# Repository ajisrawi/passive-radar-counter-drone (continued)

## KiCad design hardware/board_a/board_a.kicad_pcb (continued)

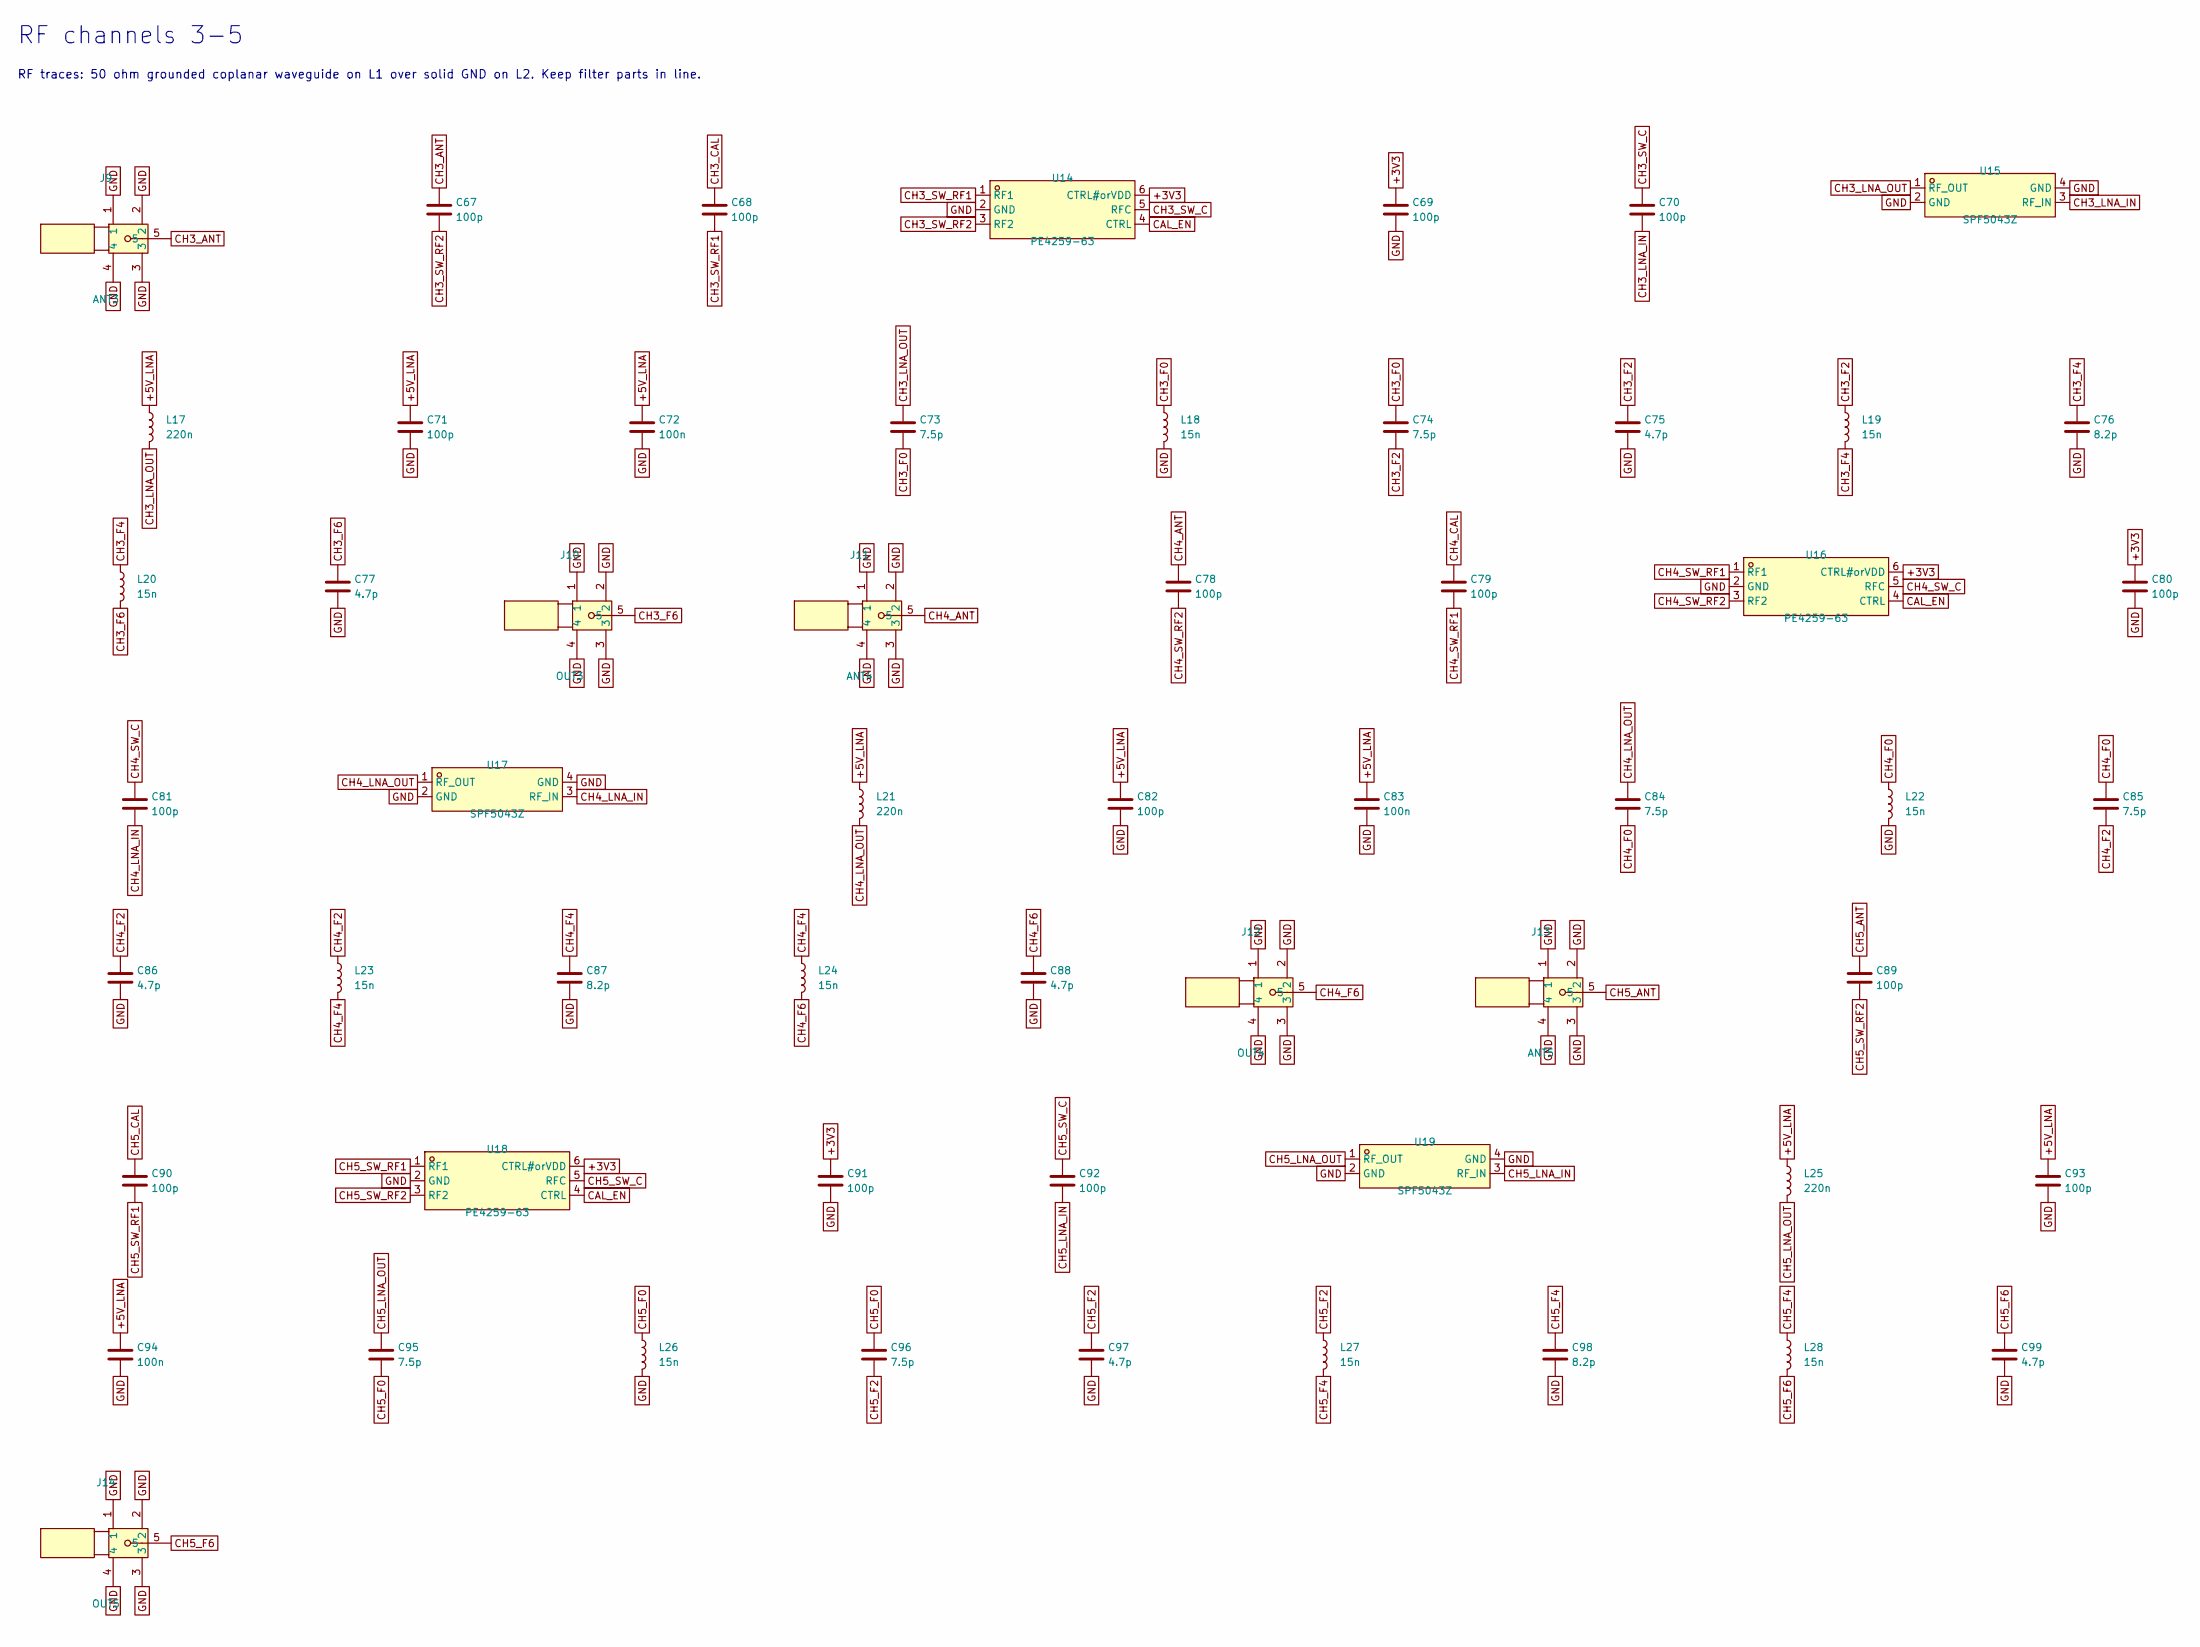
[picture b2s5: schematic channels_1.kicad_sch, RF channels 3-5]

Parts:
C67, C68, C69, C70, C71, C78, C79, C80, C81, C82, C89, C90, C91, C92, C93: 100p; C_0402_1005Metric
C72, C83, C94: 100n; C_0402_1005Metric; LCSC C1525
C73, C74, C84, C85, C95, C96: 7.5p; C_0402_1005Metric
C75, C77, C86, C88, C97, C99: 4.7p; C_0402_1005Metric
C76, C87, C98: 8.2p; C_0402_1005Metric
J9: ANT3; SMA-TH_BWSMA-KE-Z001; MPN BWSMA-KE-Z001; LCSC C496549
J10: OUT3; SMA-TH_BWSMA-KE-Z001; MPN BWSMA-KE-Z001; LCSC C496549
J11: ANT4; SMA-TH_BWSMA-KE-Z001; MPN BWSMA-KE-Z001; LCSC C496549
J12: OUT4; SMA-TH_BWSMA-KE-Z001; MPN BWSMA-KE-Z001; LCSC C496549
J13: ANT5; SMA-TH_BWSMA-KE-Z001; MPN BWSMA-KE-Z001; LCSC C496549
J14: OUT5; SMA-TH_BWSMA-KE-Z001; MPN BWSMA-KE-Z001; LCSC C496549
L17, L21, L25: 220n; L_0603_1608Metric
L18, L19, L20, L22, L23, L24, L26, L27, L28: 15n; L_0402_1005Metric
U14, U16, U18: PE4259-63; SC-70-6_L2.2-W1.3-P0.65-LS2.1-BL; MPN PE4259-63; LCSC C470892
U15, U17, U19: SPF5043Z; SOT343_L2.0-W1.3-P1.30-LS2.1-BL; MPN SPF5043Z; LCSC C470902

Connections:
+3V3: C69.1, C80.1, C91.1, U14.6 (CTRL#orVDD), U16.6 (CTRL#orVDD), U18.6 (CTRL#orVDD); also elsewhere on the board
+5V_LNA: C71.1, C72.1, C82.1, C83.1, C93.1, C94.1, L17.1, L21.1, L25.1; also elsewhere on the board
CAL_EN: U14.4 (CTRL), U16.4 (CTRL), U18.4 (CTRL); also elsewhere on the board
CH3_ANT: C67.1, J9.5
CH3_CAL: C68.1; also elsewhere on the board
CH3_F0: C73.2, C74.1, L18.1
CH3_F2: C74.2, C75.1, L19.1
CH3_F4: C76.1, L19.2, L20.1
CH3_F6: C77.1, J10.5, L20.2
CH3_LNA_IN: C70.2, U15.3 (RF_IN)
CH3_LNA_OUT: C73.1, L17.2, U15.1 (RF_OUT)
CH3_SW_C: C70.1, U14.5 (RFC)
CH3_SW_RF1: C68.2, U14.1 (RF1)
CH3_SW_RF2: C67.2, U14.3 (RF2)
CH4_ANT: C78.1, J11.5
CH4_CAL: C79.1; also elsewhere on the board
CH4_F0: C84.2, C85.1, L22.1
CH4_F2: C85.2, C86.1, L23.1
CH4_F4: C87.1, L23.2, L24.1
CH4_F6: C88.1, J12.5, L24.2
CH4_LNA_IN: C81.2, U17.3 (RF_IN)
CH4_LNA_OUT: C84.1, L21.2, U17.1 (RF_OUT)
CH4_SW_C: C81.1, U16.5 (RFC)
CH4_SW_RF1: C79.2, U16.1 (RF1)
CH4_SW_RF2: C78.2, U16.3 (RF2)
CH5_ANT: C89.1, J13.5
CH5_CAL: C90.1; also elsewhere on the board
CH5_F0: C95.2, C96.1, L26.1
CH5_F2: C96.2, C97.1, L27.1
CH5_F4: C98.1, L27.2, L28.1
CH5_F6: C99.1, J14.5, L28.2
CH5_LNA_IN: C92.2, U19.3 (RF_IN)
CH5_LNA_OUT: C95.1, L25.2, U19.1 (RF_OUT)
CH5_SW_C: C92.1, U18.5 (RFC)
CH5_SW_RF1: C90.2, U18.1 (RF1)
CH5_SW_RF2: C89.2, U18.3 (RF2)
GND: C69.2, C71.2, C72.2, C75.2, C76.2, C77.2, C80.2, C82.2, C83.2, C86.2, C87.2, C88.2, C91.2, C93.2, C94.2, C97.2, C98.2, C99.2, J9.1, J9.2, J9.3, J9.4, J10.1, J10.2, J10.3, J10.4, J11.1, J11.2, J11.3, J11.4, J12.1, J12.2, J12.3, J12.4, J13.1, J13.2, J13.3, J13.4, J14.1, J14.2, J14.3, J14.4, L18.2, L22.2, L26.2, U14.2 (GND), U15.2 (GND), U15.4 (GND), U16.2 (GND), U17.2 (GND), U17.4 (GND), U18.2 (GND), U19.2 (GND), U19.4 (GND); also elsewhere on the board

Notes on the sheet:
RF channels 3-5
RF traces: 50 ohm grounded coplanar waveguide on L1 over solid GND on L2. Keep filter parts in line.

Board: 4 copper layers, 194 parts (0 on the bottom side), 98 nets, no tracks yet.

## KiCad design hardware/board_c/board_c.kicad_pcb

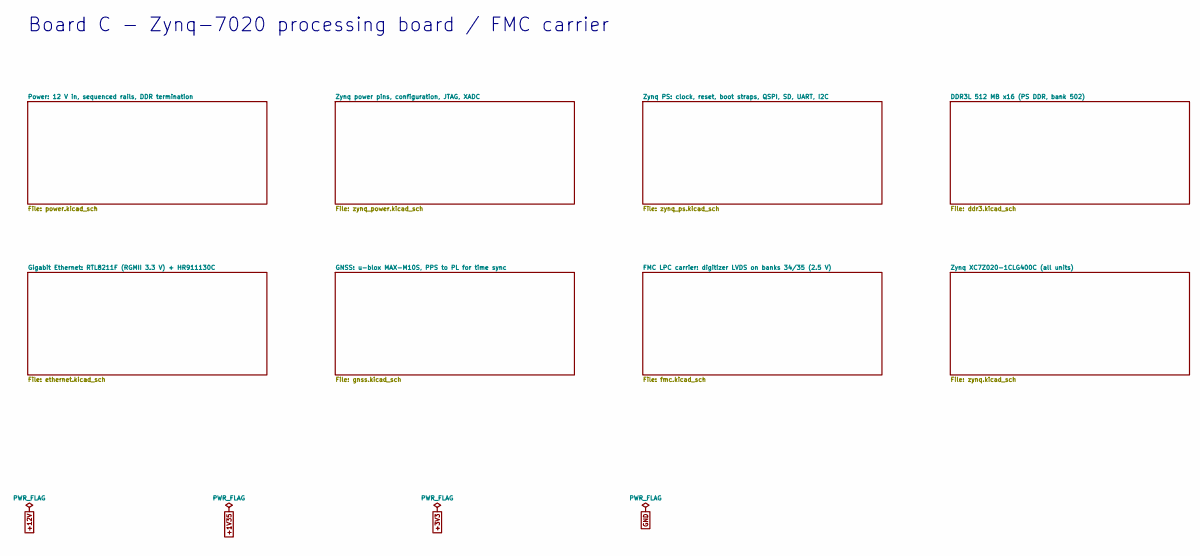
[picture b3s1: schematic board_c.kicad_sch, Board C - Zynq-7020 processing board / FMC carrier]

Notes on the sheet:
Board C - Zynq-7020 processing board / FMC carrier

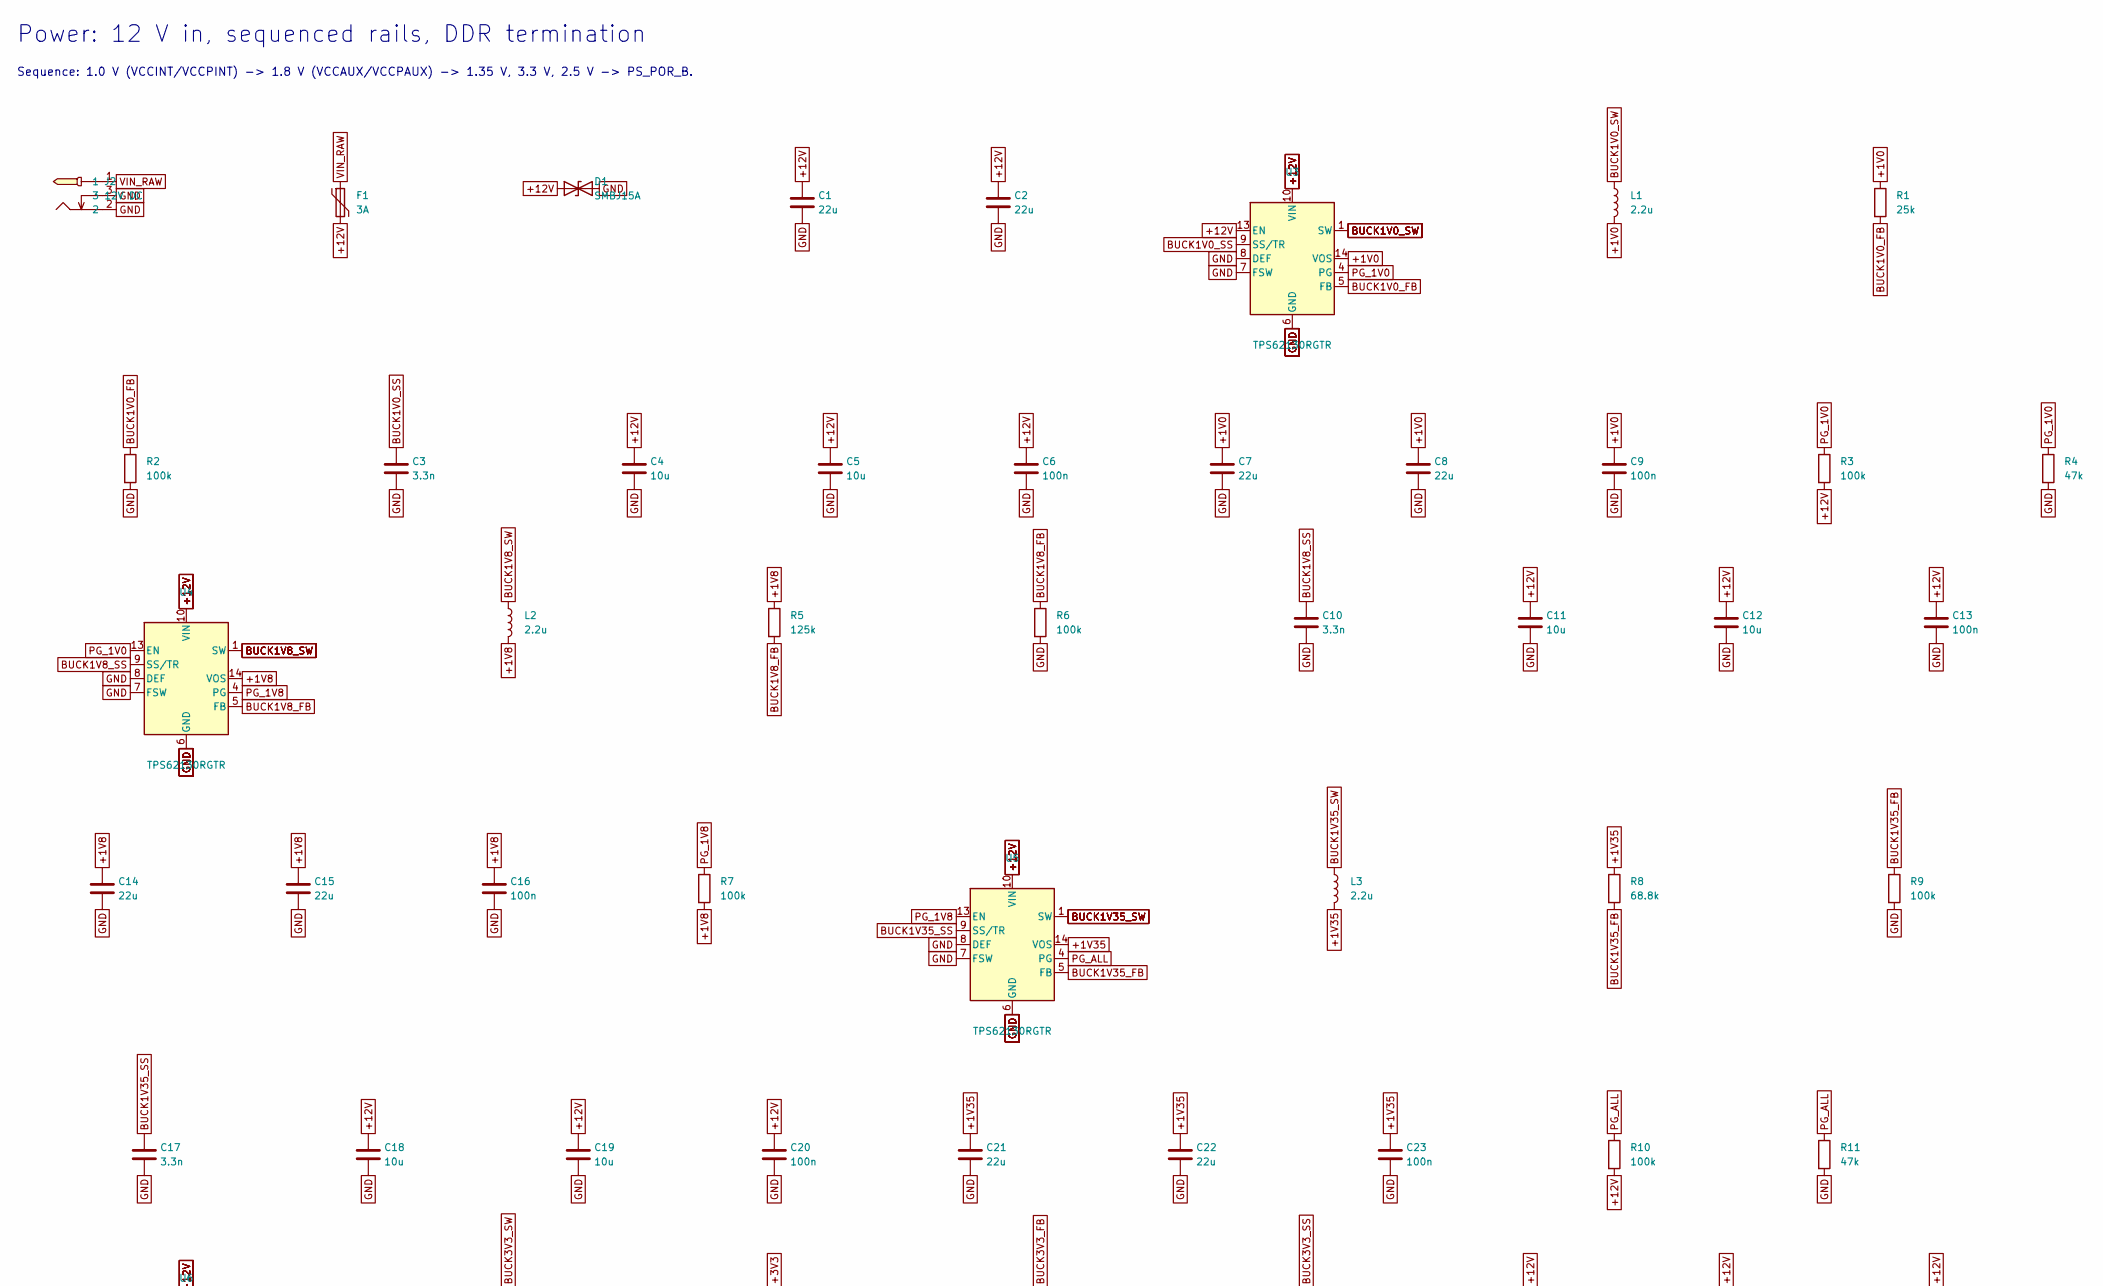
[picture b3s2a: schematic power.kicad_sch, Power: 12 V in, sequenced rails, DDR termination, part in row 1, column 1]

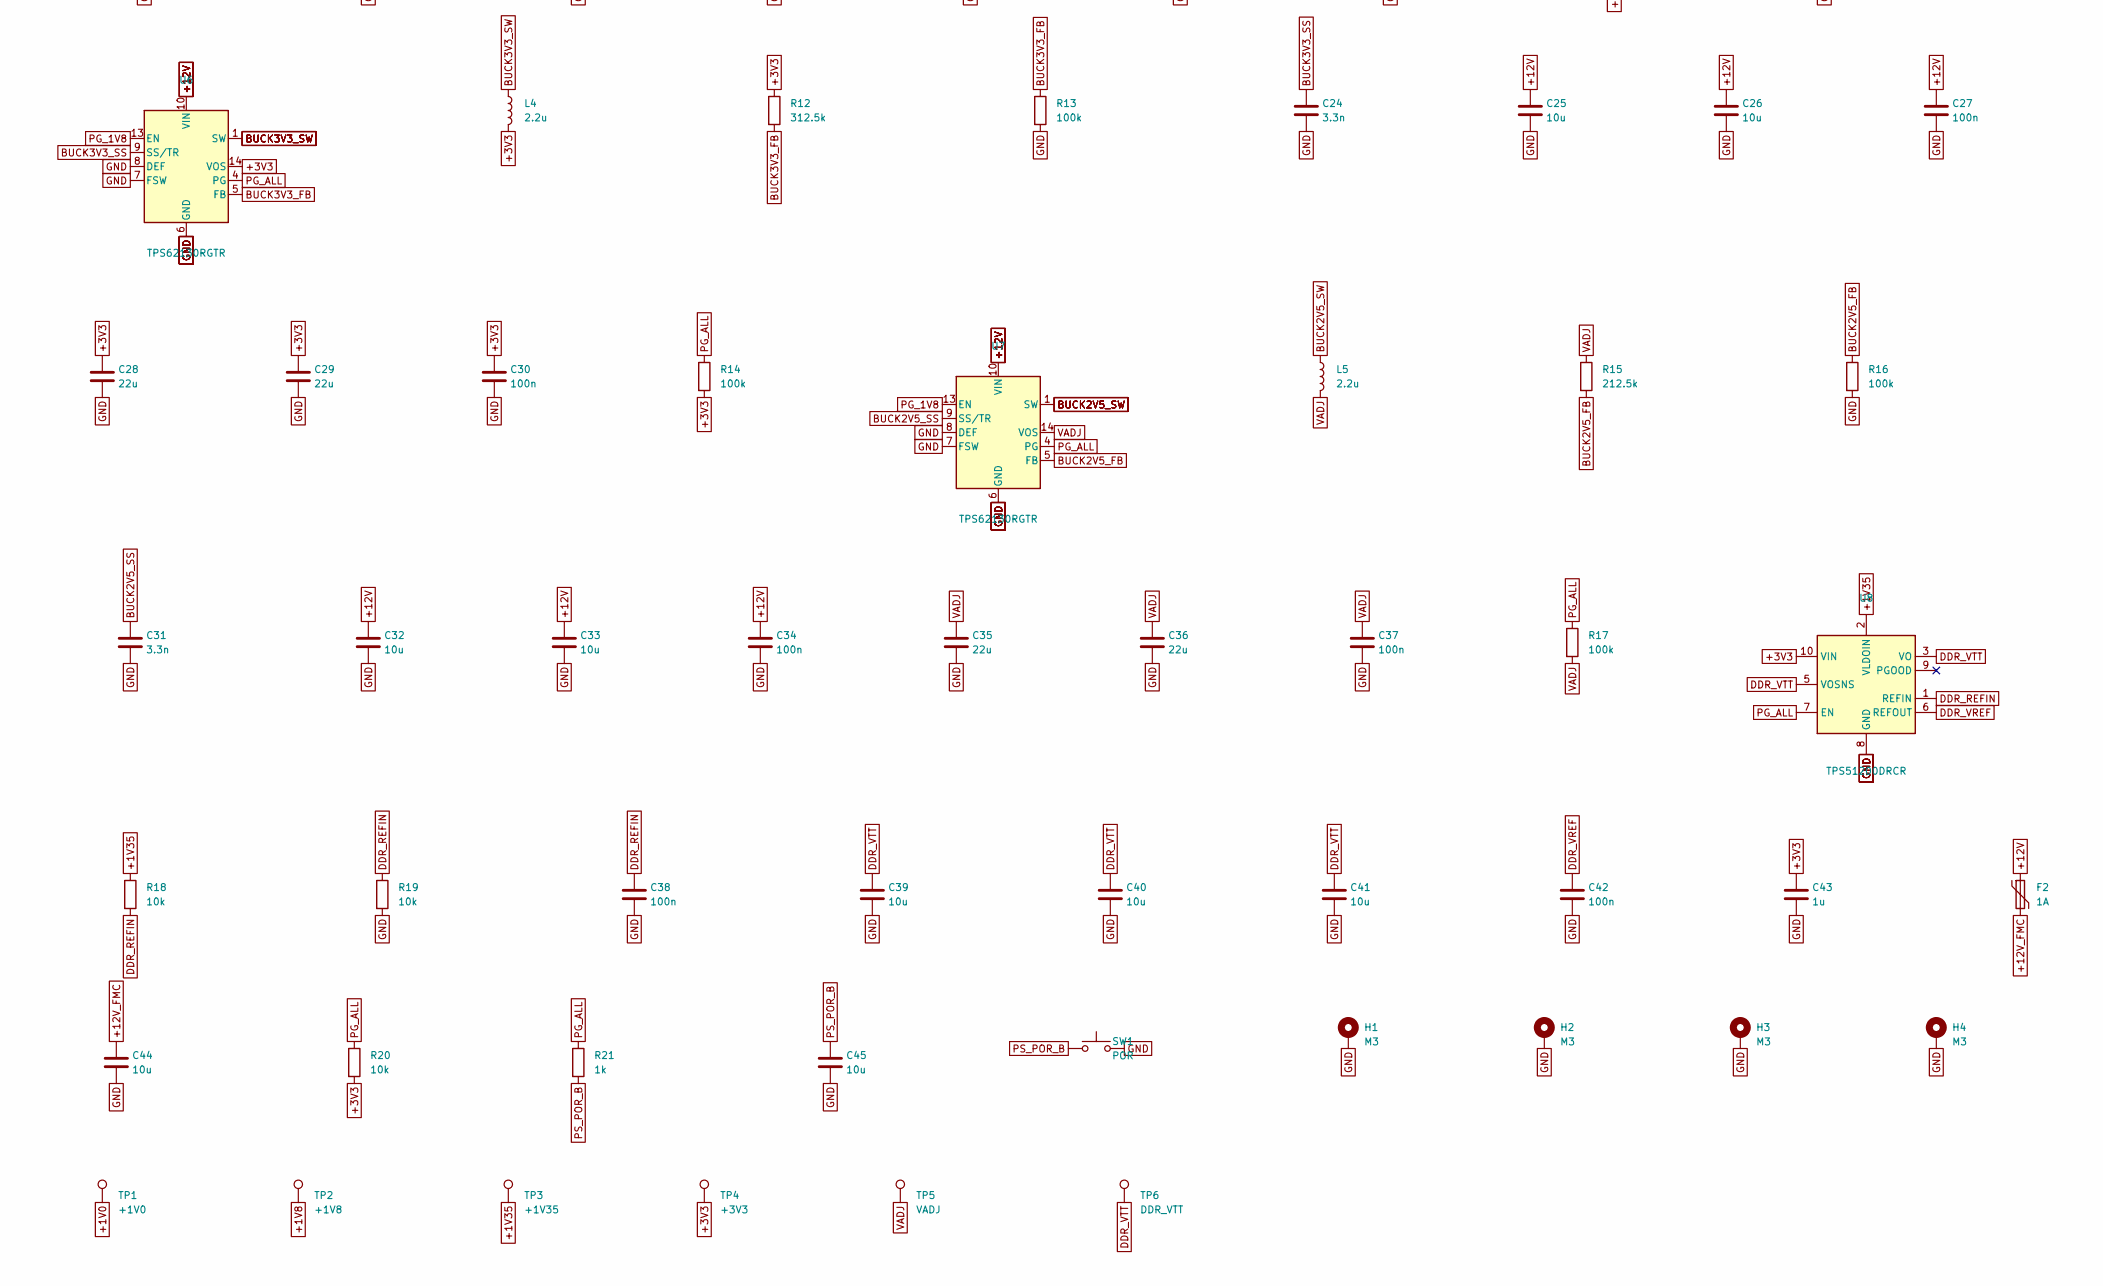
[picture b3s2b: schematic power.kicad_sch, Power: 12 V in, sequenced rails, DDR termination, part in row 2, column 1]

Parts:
C1, C2: 22u; C_1206_3216Metric
C3, C10, C17, C24, C31: 3.3n; C_0402_1005Metric
C4, C5, C11, C12, C18, C19, C25, C26, C32, C33, C44: 10u; C_0805_2012Metric
C6, C9, C13, C16, C20, C23, C27, C30, C34, C37, C38, C42: 100n; C_0402_1005Metric; LCSC C1525
C7, C8, C14, C15, C21, C22, C28, C29, C35, C36: 22u; C_0805_2012Metric; LCSC C45783
C39, C40, C41, C45: 10u; C_0603_1608Metric; LCSC C19702
C43: 1u; C_0402_1005Metric; LCSC C52923
D1: SMBJ15A; D_SMB
F1: 3A; Fuse_1206_3216Metric
F2: 1A; Fuse_1206_3216Metric
H1, H2, H3, H4: M3; MountingHole_3.2mm_M3_Pad_Via
J2: 12V DC; DC-IN-TH_DC-005C-20A; MPN DC-005C-20A; LCSC C84007
L1, L2, L3, L4, L5: 2.2u; L_Bourns-SRN4018; MPN SRN4018-2R2M
R1: 25k; R_0402_1005Metric
R2, R3, R6, R7, R9, R10, R13, R14, R16, R17: 100k; R_0402_1005Metric; LCSC C25741
R4, R11: 47k; R_0402_1005Metric
R5: 125k; R_0402_1005Metric
R8: 68.8k; R_0402_1005Metric
R12: 312.5k; R_0402_1005Metric
R15: 212.5k; R_0402_1005Metric
R18, R19: 10k; R_0402_1005Metric; Tolerance 1%; LCSC C25744
R20: 10k; R_0402_1005Metric; LCSC C25744
R21: 1k; R_0402_1005Metric; LCSC C11702
SW1: POR; SW_SPST_TL3342
TP1: +1V0; TestPoint_Pad_D1.0mm
TP2: +1V8; TestPoint_Pad_D1.0mm
TP3: +1V35; TestPoint_Pad_D1.0mm
TP4: +3V3; TestPoint_Pad_D1.0mm
TP5: VADJ; TestPoint_Pad_D1.0mm
TP6: DDR_VTT; TestPoint_Pad_D1.0mm
U3, U4, U5, U6, U7: TPS62130RGTR; VQFN-16-1EP_3x3mm_P0.5mm_EP1.68x1.68mm; MPN TPS62130RGTR; LCSC C43590
U8: TPS51200DRCR; VSON-10-1EP_3x3mm_P0.5mm_EP1.65x2.4mm; LCSC C34771

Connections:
+1V0: C7.1, C8.1, C9.1, L1.2, R1.1, TP1.1, U3.14 (VOS); also elsewhere on the board
+1V8: C14.1, C15.1, C16.1, L2.2, R5.1, R7.2, TP2.1, U4.14 (VOS); also elsewhere on the board
+1V35: C21.1, C22.1, C23.1, L3.2, R8.1, R18.1, TP3.1, U5.14 (VOS), U8.2 (VLDOIN); also elsewhere on the board
+3V3: C28.1, C29.1, C30.1, C43.1, L4.2, R12.1, R14.2, R20.2, TP4.1, U6.14 (VOS), U8.10 (VIN); also elsewhere on the board
+12V: C1.1, C2.1, C4.1, C5.1, C6.1, C11.1, C12.1, C13.1, C18.1, C19.1, C20.1, C25.1, C26.1, C27.1, C32.1, C33.1, C34.1, D1.1 (A1), F1.2, F2.1, R3.2, R10.2, U3.10 (VIN), U3.11 (VIN), U3.12 (VIN), U3.13 (EN), U4.10 (VIN), U4.11 (VIN), U4.12 (VIN), U5.10 (VIN), U5.11 (VIN), U5.12 (VIN), U6.10 (VIN), U6.11 (VIN), U6.12 (VIN), U7.10 (VIN), U7.11 (VIN), U7.12 (VIN)
+12V_FMC: C44.1, F2.2; also elsewhere on the board
BUCK1V0_FB: R1.2, R2.1, U3.5 (FB)
BUCK1V0_SS: C3.1, U3.9 (SS/TR)
BUCK1V0_SW: L1.1, U3.1 (SW), U3.2 (SW), U3.3 (SW)
BUCK1V8_FB: R5.2, R6.1, U4.5 (FB)
BUCK1V8_SS: C10.1, U4.9 (SS/TR)
BUCK1V8_SW: L2.1, U4.1 (SW), U4.2 (SW), U4.3 (SW)
BUCK1V35_FB: R8.2, R9.1, U5.5 (FB)
BUCK1V35_SS: C17.1, U5.9 (SS/TR)
BUCK1V35_SW: L3.1, U5.1 (SW), U5.2 (SW), U5.3 (SW)
BUCK2V5_FB: R15.2, R16.1, U7.5 (FB)
BUCK2V5_SS: C31.1, U7.9 (SS/TR)
BUCK2V5_SW: L5.1, U7.1 (SW), U7.2 (SW), U7.3 (SW)
BUCK3V3_FB: R12.2, R13.1, U6.5 (FB)
BUCK3V3_SS: C24.1, U6.9 (SS/TR)
BUCK3V3_SW: L4.1, U6.1 (SW), U6.2 (SW), U6.3 (SW)
DDR_REFIN: C38.1, R18.2, R19.1, U8.1 (REFIN)
DDR_VREF: C42.1, U8.6 (REFOUT); also elsewhere on the board
DDR_VTT: C39.1, C40.1, C41.1, TP6.1, U8.3 (VO), U8.5 (VOSNS); also elsewhere on the board
GND: C1.2, C2.2, C3.2, C4.2, C5.2, C6.2, C7.2, C8.2, C9.2, C10.2, C11.2, C12.2, C13.2, C14.2, C15.2, C16.2, C17.2, C18.2, C19.2, C20.2, C21.2, C22.2, C23.2, C24.2, C25.2, C26.2, C27.2, C28.2, C29.2, C30.2, C31.2, C32.2, C33.2, C34.2, C35.2, C36.2, C37.2, C38.2, C39.2, C40.2, C41.2, C42.2, C43.2, C44.2, C45.2, D1.2 (A2), H1.1, H2.1, H3.1, H4.1, J2.2, J2.3, R2.2, R4.2, R6.2, R9.2, R11.2, R13.2, R16.2, R19.2, SW1.2, U3.6 (GND), U3.7 (FSW), U3.8 (DEF), U3.15 (GND), U3.16 (GND), U3.17 (GND), U4.6 (GND), U4.7 (FSW), U4.8 (DEF), U4.15 (GND), U4.16 (GND), U4.17 (GND), U5.6 (GND), U5.7 (FSW), U5.8 (DEF), U5.15 (GND), U5.16 (GND), U5.17 (GND), U6.6 (GND), U6.7 (FSW), U6.8 (DEF), U6.15 (GND), U6.16 (GND), U6.17 (GND), U7.6 (GND), U7.7 (FSW), U7.8 (DEF), U7.15 (GND), U7.16 (GND), U7.17 (GND), U8.4 (GND), U8.8 (GND), U8.11 (GND); also elsewhere on the board
PG_1V0: R3.1, R4.1, U3.4 (PG), U4.13 (EN)
PG_1V8: R7.1, U4.4 (PG), U5.13 (EN), U6.13 (EN), U7.13 (EN)
PG_ALL: R10.1, R11.1, R14.1, R17.1, R20.1, R21.1, U5.4 (PG), U6.4 (PG), U7.4 (PG), U8.7 (EN); also elsewhere on the board
PS_POR_B: C45.1, R21.2, SW1.1; also elsewhere on the board
VADJ: C35.1, C36.1, C37.1, L5.2, R15.1, R17.2, TP5.1, U7.14 (VOS); also elsewhere on the board
VIN_RAW: F1.1, J2.1

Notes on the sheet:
Power: 12 V in, sequenced rails, DDR termination
Sequence: 1.0 V (VCCINT/VCCPINT) -> 1.8 V (VCCAUX/VCCPAUX) -> 1.35 V, 3.3 V, 2.5 V -> PS_POR_B.

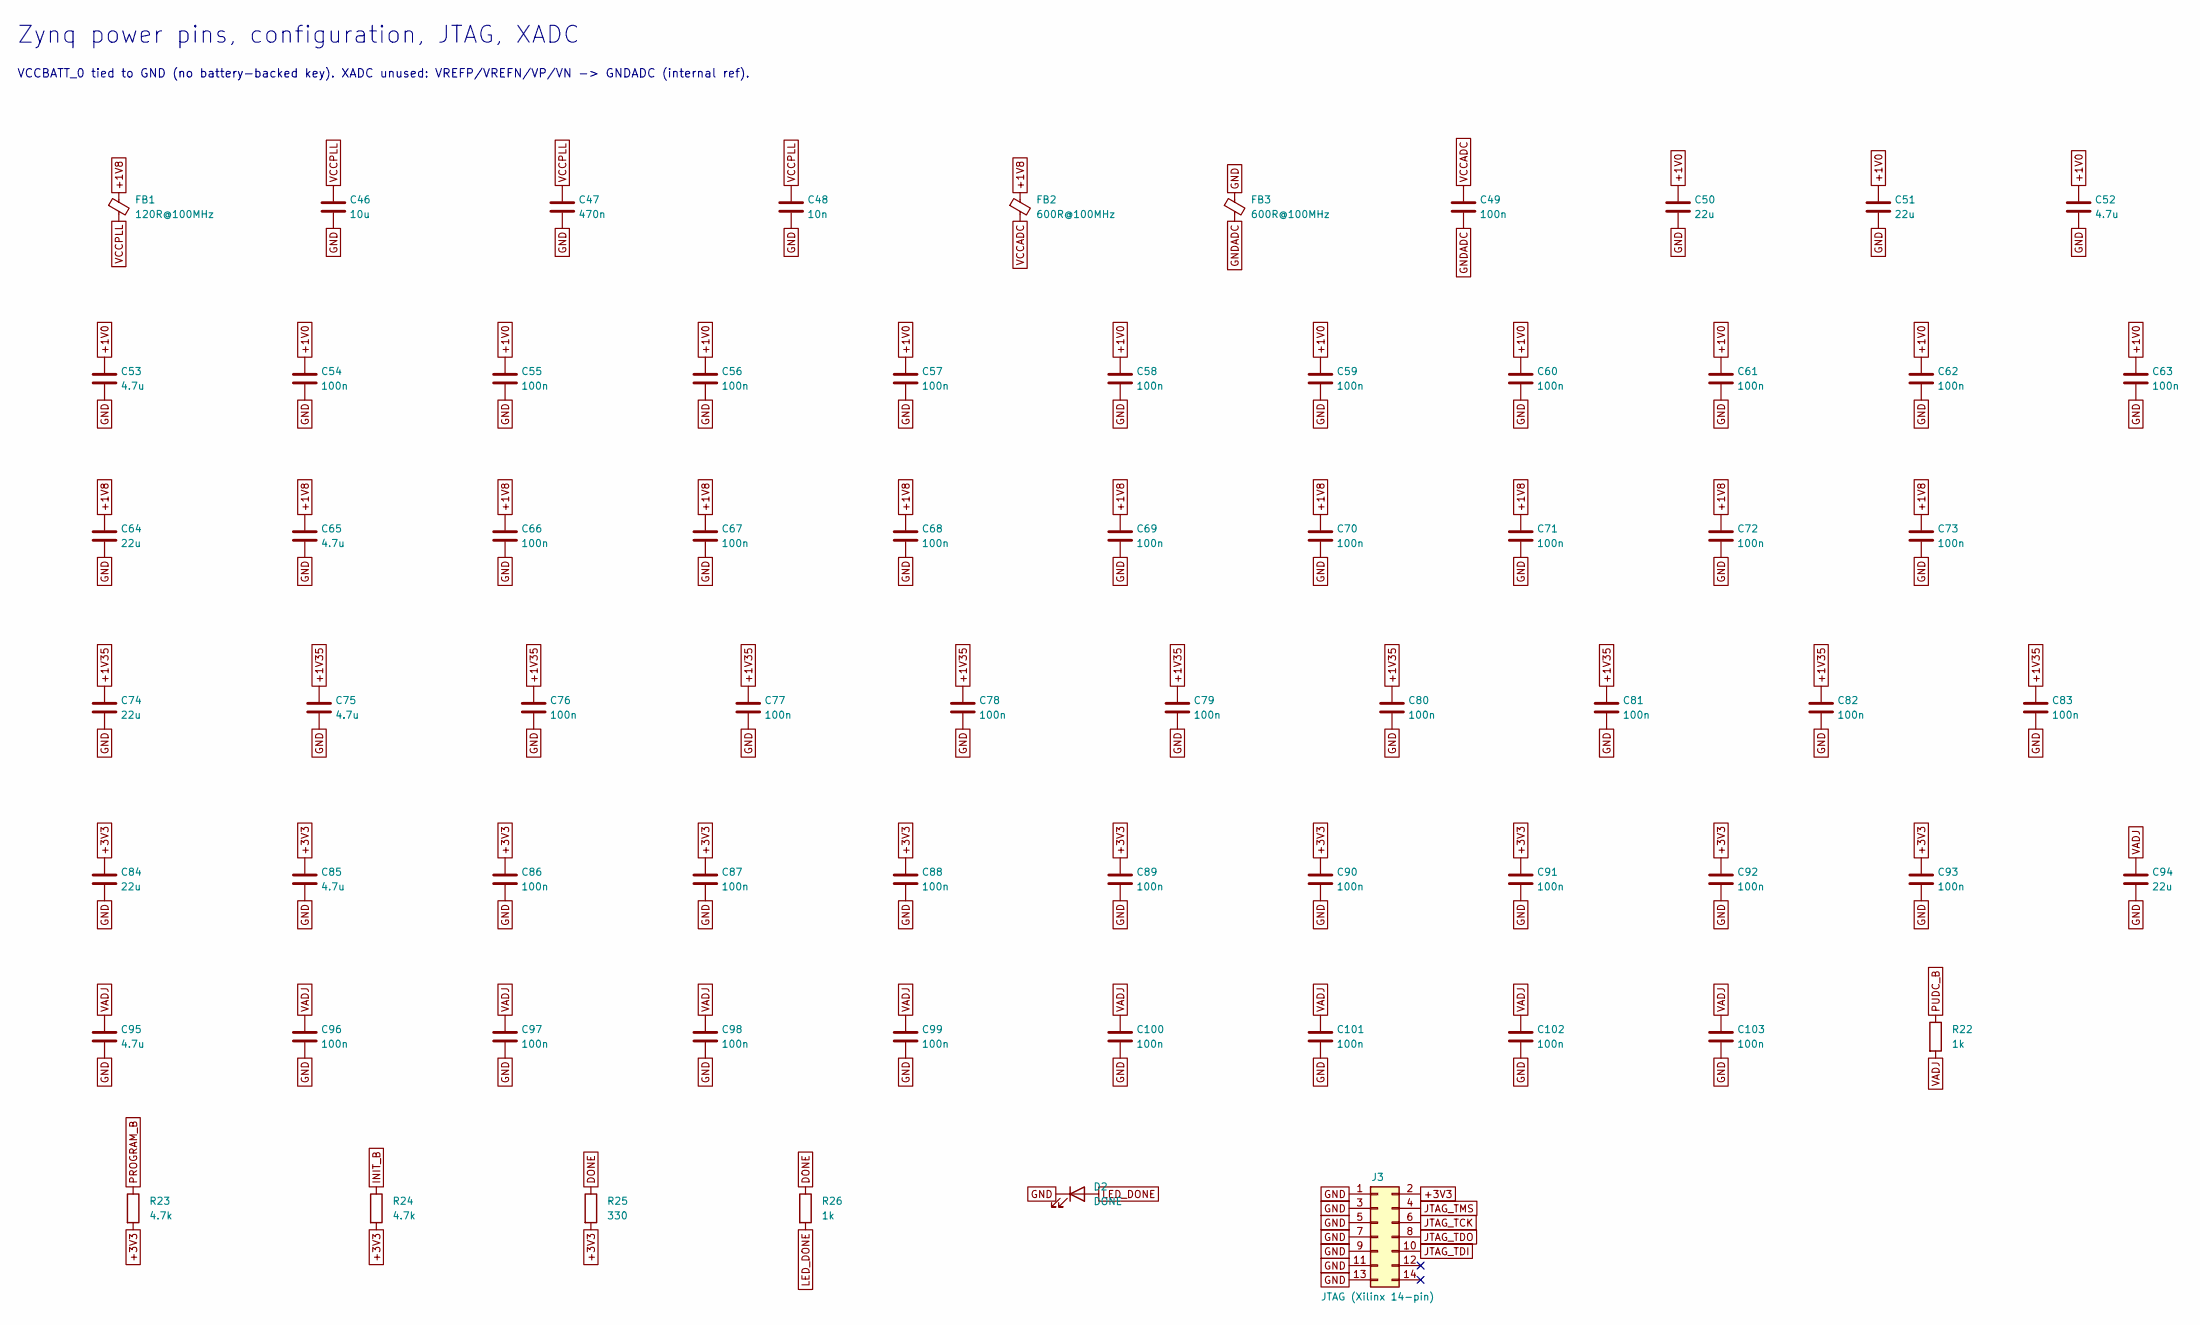
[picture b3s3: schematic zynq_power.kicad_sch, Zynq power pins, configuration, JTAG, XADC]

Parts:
C46: 10u; C_0603_1608Metric; LCSC C19702
C47: 470n; C_0402_1005Metric
C48: 10n; C_0402_1005Metric; LCSC C15195
C49, C54, C55, C56, C57, C58, C59, C60, C61, C62, C63, C66, C67, C68, C69, C70, C71, C72, C73, C76, C77, C78, C79, C80, C81, C82, C83, C86, C87, C88, C89, C90, C91, C92, C93, C96, C97, C98, C99, C100, C101, C102, C103: 100n; C_0402_1005Metric; LCSC C1525
C50, C51, C64, C74, C84, C94: 22u; C_0805_2012Metric; LCSC C45783
C52, C53, C65, C75, C85, C95: 4.7u; C_0603_1608Metric
D2: DONE; LED_0603_1608Metric
FB1: 120R@100MHz; L_0603_1608Metric
FB2, FB3: 600R@100MHz; L_0603_1608Metric
J3: JTAG (Xilinx 14-pin); PinHeader_2x07_P2.00mm_Vertical
R22, R26: 1k; R_0402_1005Metric; LCSC C11702
R23, R24: 4.7k; R_0402_1005Metric; LCSC C25900
R25: 330; R_0402_1005Metric

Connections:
+1V0: C50.1, C51.1, C52.1, C53.1, C54.1, C55.1, C56.1, C57.1, C58.1, C59.1, C60.1, C61.1, C62.1, C63.1; also elsewhere on the board
+1V8: C64.1, C65.1, C66.1, C67.1, C68.1, C69.1, C70.1, C71.1, C72.1, C73.1, FB1.1, FB2.1; also elsewhere on the board
+1V35: C74.1, C75.1, C76.1, C77.1, C78.1, C79.1, C80.1, C81.1, C82.1, C83.1; also elsewhere on the board
+3V3: C84.1, C85.1, C86.1, C87.1, C88.1, C89.1, C90.1, C91.1, C92.1, C93.1, J3.2, R23.2, R24.2, R25.2; also elsewhere on the board
DONE: R25.1, R26.1; also elsewhere on the board
GND: C46.2, C47.2, C48.2, C50.2, C51.2, C52.2, C53.2, C54.2, C55.2, C56.2, C57.2, C58.2, C59.2, C60.2, C61.2, C62.2, C63.2, C64.2, C65.2, C66.2, C67.2, C68.2, C69.2, C70.2, C71.2, C72.2, C73.2, C74.2, C75.2, C76.2, C77.2, C78.2, C79.2, C80.2, C81.2, C82.2, C83.2, C84.2, C85.2, C86.2, C87.2, C88.2, C89.2, C90.2, C91.2, C92.2, C93.2, C94.2, C95.2, C96.2, C97.2, C98.2, C99.2, C100.2, C101.2, C102.2, C103.2, D2.1 (K), FB3.1, J3.1, J3.3, J3.5, J3.7, J3.9, J3.11, J3.13; also elsewhere on the board
GNDADC: C49.2, FB3.2; also elsewhere on the board
INIT_B: R24.1; also elsewhere on the board
JTAG_TCK: J3.6; also elsewhere on the board
JTAG_TDI: J3.10; also elsewhere on the board
JTAG_TDO: J3.8; also elsewhere on the board
JTAG_TMS: J3.4; also elsewhere on the board
LED_DONE: D2.2 (A), R26.2
PROGRAM_B: R23.1; also elsewhere on the board
PUDC_B: R22.1; also elsewhere on the board
VADJ: C94.1, C95.1, C96.1, C97.1, C98.1, C99.1, C100.1, C101.1, C102.1, C103.1, R22.2; also elsewhere on the board
VCCADC: C49.1, FB2.2; also elsewhere on the board
VCCPLL: C46.1, C47.1, C48.1, FB1.2; also elsewhere on the board

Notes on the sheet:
Zynq power pins, configuration, JTAG, XADC
VCCBATT_0 tied to GND (no battery-backed key). XADC unused: VREFP/VREFN/VP/VN -> GNDADC (internal ref).
